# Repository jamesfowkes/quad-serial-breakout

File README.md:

# quad-serial-breakout
A quad USB-to-serial breakout board based on the FT4232 IC

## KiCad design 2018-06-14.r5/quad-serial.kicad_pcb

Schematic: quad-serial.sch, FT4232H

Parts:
BRD1: BOARD; DP5050

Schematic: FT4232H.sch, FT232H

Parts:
C1, C4: 22p; C_0603
C2, C3: 4u7; C_0603
C5, C6, C7, C8, C10, C11, C12: 100n; C_0603
L1, L2: 220nH; R_0603
R1: 12K; R_0603
R2: 1K; R_0603
U6: FT4232H-56Q; QFN-56-1EP_8x8mm_Pitch0.5mm
X1: CRYSTAL; 5032+HC49

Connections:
+1.8V: C7.1, C8.1, U6.2, U6.31, U6.43
+3V3: C10.1, C11.1, C12.1, L1.1, L2.1, R2.2, U6.16, U6.36, U6.44, U6.50; also elsewhere on the board
/FT4232H/CTSA: U6.15; also elsewhere on the board
/FT4232H/CTSB: U6.25; also elsewhere on the board
/FT4232H/CTSC: U6.35; also elsewhere on the board
/FT4232H/CTSD: U6.48; also elsewhere on the board
/FT4232H/DCDA: U6.19; also elsewhere on the board
/FT4232H/DCDB: U6.28; also elsewhere on the board
/FT4232H/DCDC: U6.39; also elsewhere on the board
/FT4232H/DCDD: U6.52; also elsewhere on the board
/FT4232H/DM: U6.7; also elsewhere on the board
/FT4232H/DP: U6.8; also elsewhere on the board
/FT4232H/DSRA: U6.18; also elsewhere on the board
/FT4232H/DSRB: U6.27; also elsewhere on the board
/FT4232H/DSRC: U6.38; also elsewhere on the board
/FT4232H/DSRD: U6.51; also elsewhere on the board
/FT4232H/DTRA: U6.17; also elsewhere on the board
/FT4232H/DTRB: U6.26; also elsewhere on the board
/FT4232H/DTRC: U6.37; also elsewhere on the board
/FT4232H/DTRD: U6.49; also elsewhere on the board
/FT4232H/LED_CLK: U6.56; also elsewhere on the board
/FT4232H/LED_CS: U6.1; also elsewhere on the board
/FT4232H/LED_DATA: U6.55; also elsewhere on the board
/FT4232H/OSCI: C1.1, U6.3, X1.2
/FT4232H/OSCO: C4.1, U6.4, X1.1
/FT4232H/REF: R1.1, U6.6
/FT4232H/RESET: R2.1, U6.11
/FT4232H/RIA: U6.20; also elsewhere on the board
/FT4232H/RIB: U6.29; also elsewhere on the board
/FT4232H/RIC: U6.40; also elsewhere on the board
/FT4232H/RID: U6.53; also elsewhere on the board
/FT4232H/RTSA: U6.14; also elsewhere on the board
/FT4232H/RTSB: U6.24; also elsewhere on the board
/FT4232H/RTSC: U6.34; also elsewhere on the board
/FT4232H/RTSD: U6.47; also elsewhere on the board
/FT4232H/RXDA: U6.13; also elsewhere on the board
/FT4232H/RXDB: U6.23; also elsewhere on the board
/FT4232H/RXDC: U6.33; also elsewhere on the board
/FT4232H/RXDD: U6.46; also elsewhere on the board
/FT4232H/TXDA: U6.12; also elsewhere on the board
/FT4232H/TXDB: U6.22; also elsewhere on the board
/FT4232H/TXDC: U6.32; also elsewhere on the board
/FT4232H/TXDD: U6.42; also elsewhere on the board
/FT4232H/VPHY: C3.1, C6.1, L2.2, U6.5
/FT4232H/VPLL: C2.1, C5.1, L1.2, U6.9
/FT4232H/~LED_EN: U6.54; also elsewhere on the board

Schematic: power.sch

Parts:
C15, C16: 100n; C_0603
C18: 10u; C_0603
D1: D; D_SOD-123F
P5: CONN_01X02; Socket_Strip_Straight_2x01_Pitch2.54mm
U2: NCP1117ST33T3G; SOT-223

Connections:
+3V3: C16.1, U2.2 (VO); also elsewhere on the board
VEXT: D1.1, P5.1; also elsewhere on the board
VUSB: C15.1, C18.1, D1.2, U2.3 (VI); also elsewhere on the board

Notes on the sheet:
Forward current >= 1A

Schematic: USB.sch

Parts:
C14: 4n7; C_0603
J1: USB-MINI-B-SMD; USB-MICRO-B-SMD
L3: 220R@100MHz; R_0603
R3: 1M; R_0603
U3: PRTR5V0U2X; SOT-143

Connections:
/FT4232H/DM: J1.2 (D-), U3.2 (IO1); also elsewhere on the board
/FT4232H/DP: J1.3 (D+), U3.3 (IO2); also elsewhere on the board
/USB/SHIELD: C14.1, J1.6 (SHIELD), R3.1
unnamed: J1.1 (VBUS), L3.2
VUSB: L3.1, U3.4 (VCC); also elsewhere on the board

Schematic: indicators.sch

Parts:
C17: 100n; C_0603
P1, P2, P3, P4: CONN_12; Pin_Header_Straight_1x12
R4: 10K; R_0603
RP1: 1K5; R_Array_Convex_4x0603
RP2: 330R; R_Array_Convex_4x0603
RX1, RX2, RX3, RX4: LED; LED_0603
TX1, TX2, TX3, TX4: LED; LED_0603
U4: 74HC595; TSSOP-16_4.4x5mm_Pitch0.65mm

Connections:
+3V3: C17.1, P1.2, P2.2, P3.2, P4.2, R4.1, U4.16; also elsewhere on the board
/FT4232H/CTSA: P1.7; also elsewhere on the board
/FT4232H/CTSB: P2.7; also elsewhere on the board
/FT4232H/CTSC: P3.7; also elsewhere on the board
/FT4232H/CTSD: P4.7; also elsewhere on the board
/FT4232H/DCDA: P1.10; also elsewhere on the board
/FT4232H/DCDB: P2.10; also elsewhere on the board
/FT4232H/DCDC: P3.10; also elsewhere on the board
/FT4232H/DCDD: P4.10; also elsewhere on the board
/FT4232H/DSRA: P1.9; also elsewhere on the board
/FT4232H/DSRB: P2.9; also elsewhere on the board
/FT4232H/DSRC: P3.9; also elsewhere on the board
/FT4232H/DSRD: P4.9; also elsewhere on the board
/FT4232H/DTRA: P1.8; also elsewhere on the board
/FT4232H/DTRB: P2.8; also elsewhere on the board
/FT4232H/DTRC: P3.8; also elsewhere on the board
/FT4232H/DTRD: P4.8; also elsewhere on the board
/FT4232H/LED_CLK: U4.11; also elsewhere on the board
/FT4232H/LED_CS: U4.12; also elsewhere on the board
/FT4232H/LED_DATA: U4.14; also elsewhere on the board
/FT4232H/RIA: P1.11; also elsewhere on the board
/FT4232H/RIB: P2.11; also elsewhere on the board
/FT4232H/RIC: P3.11; also elsewhere on the board
/FT4232H/RID: P4.11; also elsewhere on the board
/FT4232H/RTSA: P1.6; also elsewhere on the board
/FT4232H/RTSB: P2.6; also elsewhere on the board
/FT4232H/RTSC: P3.6; also elsewhere on the board
/FT4232H/RTSD: P4.6; also elsewhere on the board
/FT4232H/RXDA: P1.4; also elsewhere on the board
/FT4232H/RXDB: P2.4; also elsewhere on the board
/FT4232H/RXDC: P3.4; also elsewhere on the board
/FT4232H/RXDD: P4.4; also elsewhere on the board
/FT4232H/TXDA: P1.3; also elsewhere on the board
/FT4232H/TXDB: P2.3; also elsewhere on the board
/FT4232H/TXDC: P3.3; also elsewhere on the board
/FT4232H/TXDD: P4.3; also elsewhere on the board
/FT4232H/~LED_EN: U4.13; also elsewhere on the board
unnamed: R4.2, U4.10
unnamed: RP1.1, TX1.2
unnamed: RP1.2, TX2.2
unnamed: RP1.3, TX3.2
unnamed: RP1.4, TX4.2
unnamed: RP1.5, U4.6
unnamed: RP1.6, U4.4
unnamed: RP1.7, U4.2
unnamed: RP1.8, U4.15
unnamed: RP2.1, RX1.2
unnamed: RP2.2, RX2.2
unnamed: RP2.3, RX3.2
unnamed: RP2.4, RX4.2
unnamed: RP2.5, U4.7
unnamed: RP2.6, U4.5
unnamed: RP2.7, U4.3
unnamed: RP2.8, U4.1
VEXT: P1.1, P2.1, P3.1, P4.1; also elsewhere on the board

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
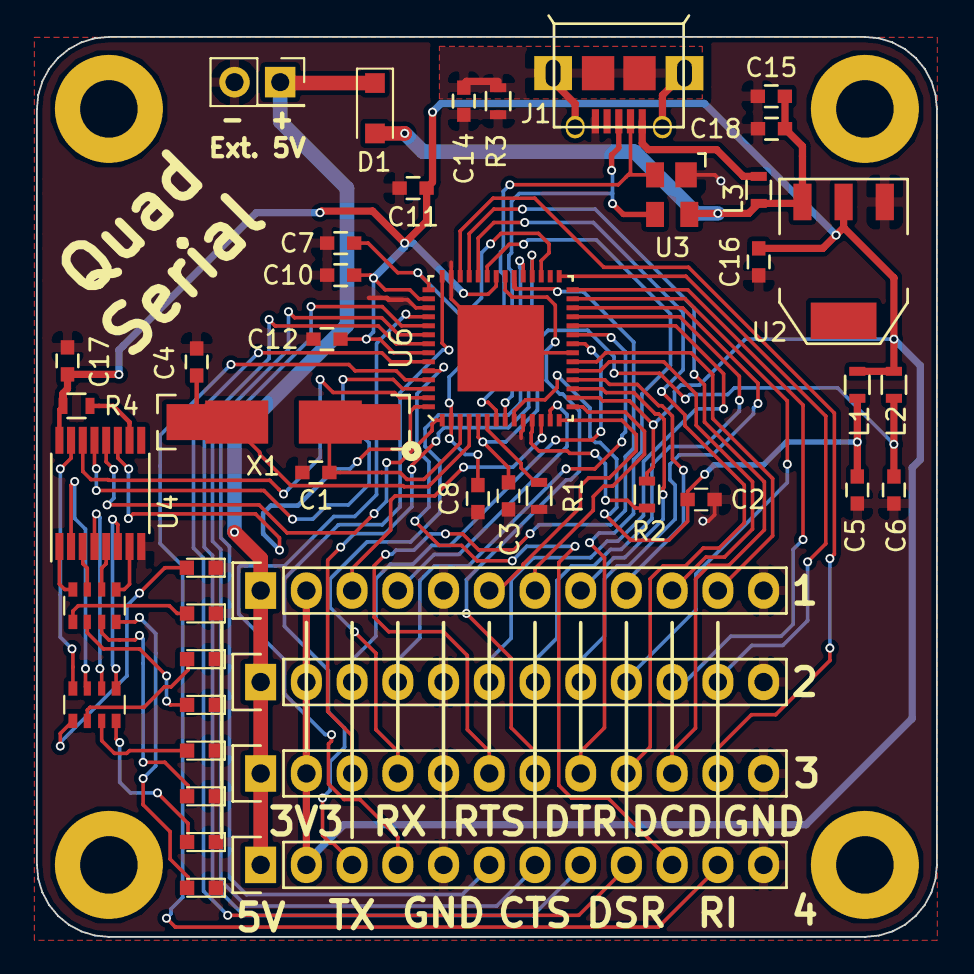
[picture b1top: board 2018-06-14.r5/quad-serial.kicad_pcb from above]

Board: 2 copper layers, 50.0 x 50.0 mm, 46 parts (0 on the bottom side), 68 nets.

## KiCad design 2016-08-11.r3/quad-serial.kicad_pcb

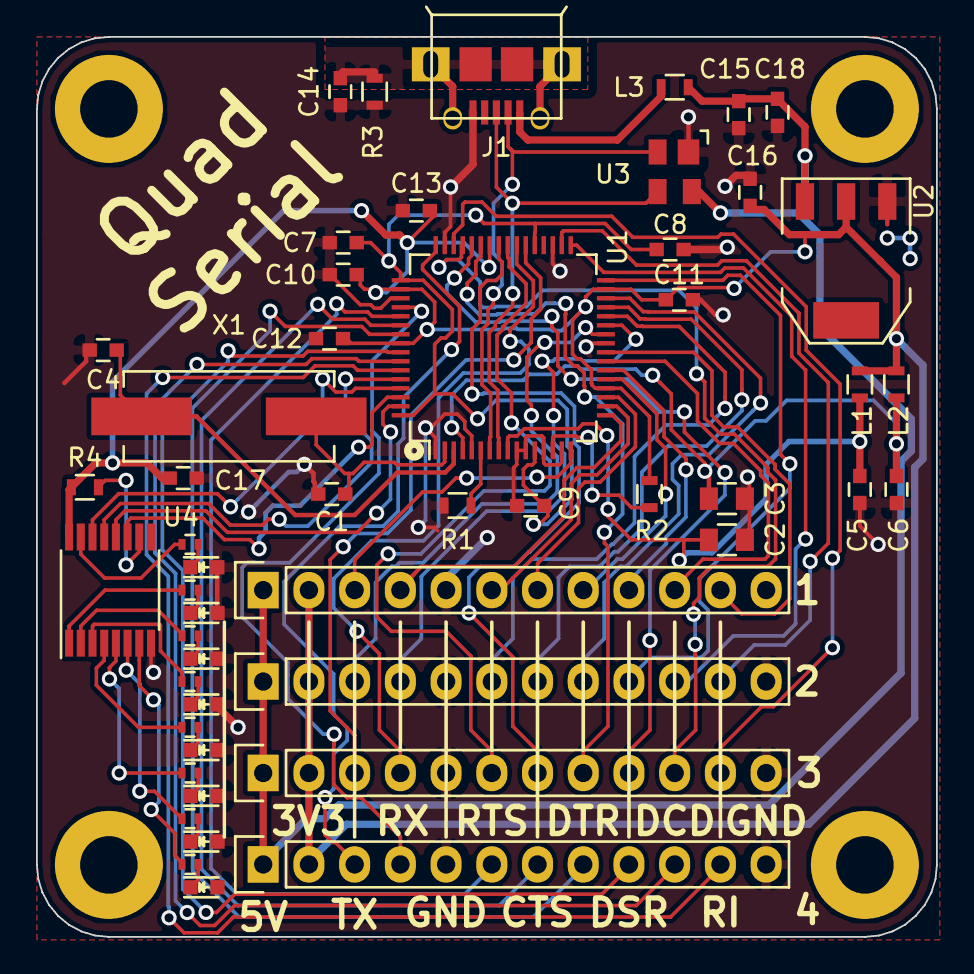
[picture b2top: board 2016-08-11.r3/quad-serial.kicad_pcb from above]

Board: 2 copper layers, 50.0 x 50.0 mm, 51 parts (0 on the bottom side), 67 nets.

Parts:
C1, C4: 22p; C_0603
C2, C3: 4u7; C_0805
C5, C6, C7, C8, C9, C10, C11, C12, C13, C15, C16, C17: 100n; C_0603
C14: 4n7; C_0603
C18: 10u; C_0603
J1: USB-MINI-B-SMD; USB-MICRO-B-SMD
L1, L2: 220nH; R_0603
L3: 220R@100MHz; R_0603
P1, P2, P3, P4: CONN_12; Pin_Header_Straight_1x12
R1: 12K; R_0603
R2: 1K; R_0603
R3: 1M; R_0603
R4: 10K; R_0603
R5, R6, R7, R8, R9, R10, R11, R12: 10K; R_0402
RX1, RX2, RX3, RX4: GRN; LED-0603
TX1, TX2, TX3, TX4: RED; LED-0603
U1: FT4232H; LQFP-64_10x10mm_Pitch0.5mm
U2: NCP1117ST33T3G; SOT-223
U3: PRTR5V0U2X; SOT-143
U4: 74HC595; TSSOP-16_4.4x5mm_Pitch0.65mm
X1: CRYSTAL; Crystal_HC49-SD_SMD

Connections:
+1.8V: C7.1, C8.1, C9.1, U1.12, U1.37, U1.49, U1.64
+3.3V: C10.1, C11.1, C12.1, C13.1, C16.1, C17.1, L1.1, L2.1, P1.2, P2.2, P3.2, P4.2, R2.2, R4.1, U1.20, U1.31, U1.42, U1.50, U1.56, U2.2, U4.16
+5V: C15.1, C18.1, L3.1, P1.1, P2.1, P3.1, P4.1, U2.3, U3.4
/FT4232H/CTSA: P1.7, U1.19
/FT4232H/CTSB: P2.7, U1.29
/FT4232H/CTSC: P3.7, U1.41
/FT4232H/CTSD: P4.7, U1.54
/FT4232H/DCDA: P1.10, U1.23
/FT4232H/DCDB: P2.10, U1.33
/FT4232H/DCDC: P3.10, U1.45
/FT4232H/DCDD: P4.10, U1.58
/FT4232H/DM: J1.2, U1.7, U3.2
/FT4232H/DP: J1.3, U1.8, U3.3
/FT4232H/DSRA: P1.9, U1.22
/FT4232H/DSRB: P2.9, U1.32
/FT4232H/DSRC: P3.9, U1.44
/FT4232H/DSRD: P4.9, U1.57
/FT4232H/DTRA: P1.8, U1.21
/FT4232H/DTRB: P2.8, U1.30
/FT4232H/DTRC: P3.8, U1.43
/FT4232H/DTRD: P4.8, U1.55
/FT4232H/LED_CLK: U1.62, U4.11
/FT4232H/LED_CS: U1.63, U4.12
/FT4232H/LED_DATA: U1.61, U4.14
/FT4232H/RIA: P1.11, U1.24
/FT4232H/RIB: P2.11, U1.34
/FT4232H/RIC: P3.11, U1.46
/FT4232H/RID: P4.11, U1.59
/FT4232H/RTSA: P1.6, U1.18
/FT4232H/RTSB: P2.6, U1.28
/FT4232H/RTSC: P3.6, U1.40
/FT4232H/RTSD: P4.6, U1.53
/FT4232H/RXDA: P1.4, U1.17
/FT4232H/RXDB: P2.4, U1.27
/FT4232H/RXDC: P3.4, U1.39
/FT4232H/RXDD: P4.4, U1.52
/FT4232H/TXDA: P1.3, U1.16
/FT4232H/TXDB: P2.3, U1.26
/FT4232H/TXDC: P3.3, U1.38
/FT4232H/TXDD: P4.3, U1.48
/FT4232H/~LED_EN: U1.60, U4.13
/USB/SHIELD: C14.1, J1.6, R3.1
GND: C1.2, C2.2, C3.2, C4.2, C5.2, C6.2, C7.2, C8.2, C9.2, C10.2, C11.2, C12.2, C13.2, C14.2, C15.2, C16.2, C17.2, C18.2, J1.5, P1.5, P1.12, P2.5, P2.12, P3.5, P3.12, P4.5, P4.12, R1.2, R3.2, RX1.2, RX2.2, RX3.2, RX4.2, TX1.2, TX2.2, TX3.2, TX4.2, U1.1, U1.5, U1.10, U1.11, U1.13, U1.15, U1.25, U1.35, U1.47, U1.51, U2.1, U3.1, U4.8
unnamed: C1.1, U1.2, X1.2
unnamed: C2.1, C5.1, L1.2, U1.9
unnamed: C3.1, C6.1, L2.2, U1.4
unnamed: C4.1, U1.3, X1.1
unnamed: J1.1, L3.2
unnamed: R1.1, U1.6
unnamed: R2.1, U1.14
unnamed: R4.2, U4.10
unnamed: R5.1, TX1.1
unnamed: R5.2, U4.15
unnamed: R6.1, RX1.1
unnamed: R6.2, U4.1
unnamed: R7.1, TX2.1
unnamed: R7.2, U4.2
unnamed: R8.1, RX2.1
unnamed: R8.2, U4.3
unnamed: R9.1, TX3.1
unnamed: R9.2, U4.4
unnamed: R10.1, RX3.1
unnamed: R10.2, U4.5
unnamed: R11.1, TX4.1
unnamed: R11.2, U4.6
unnamed: R12.1, RX4.1
unnamed: R12.2, U4.7

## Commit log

2016-07-17 First commit of project
2018-08-05 Latest project files
